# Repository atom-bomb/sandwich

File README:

Sandwich is a project to create low-cost electronics for 3D printing and CNC using an ATMEGA644p and TB6600 stepper drivers, not entirely unlike http://www.reprap.org/wiki/Gen7T and http://www.reprap.org/wiki/Sanguish.

The goal is to make an easily built, free and open design capable of running the Marlin firmware that can be built for around $40.

Design work is currently being done in the hobbyist-friendly Eagle CAD.
If the design exceeds the limits of the free version of Eagle CAD, the design will likely be ported to gEDA or another free CAD system in order to support the free and open design goal.

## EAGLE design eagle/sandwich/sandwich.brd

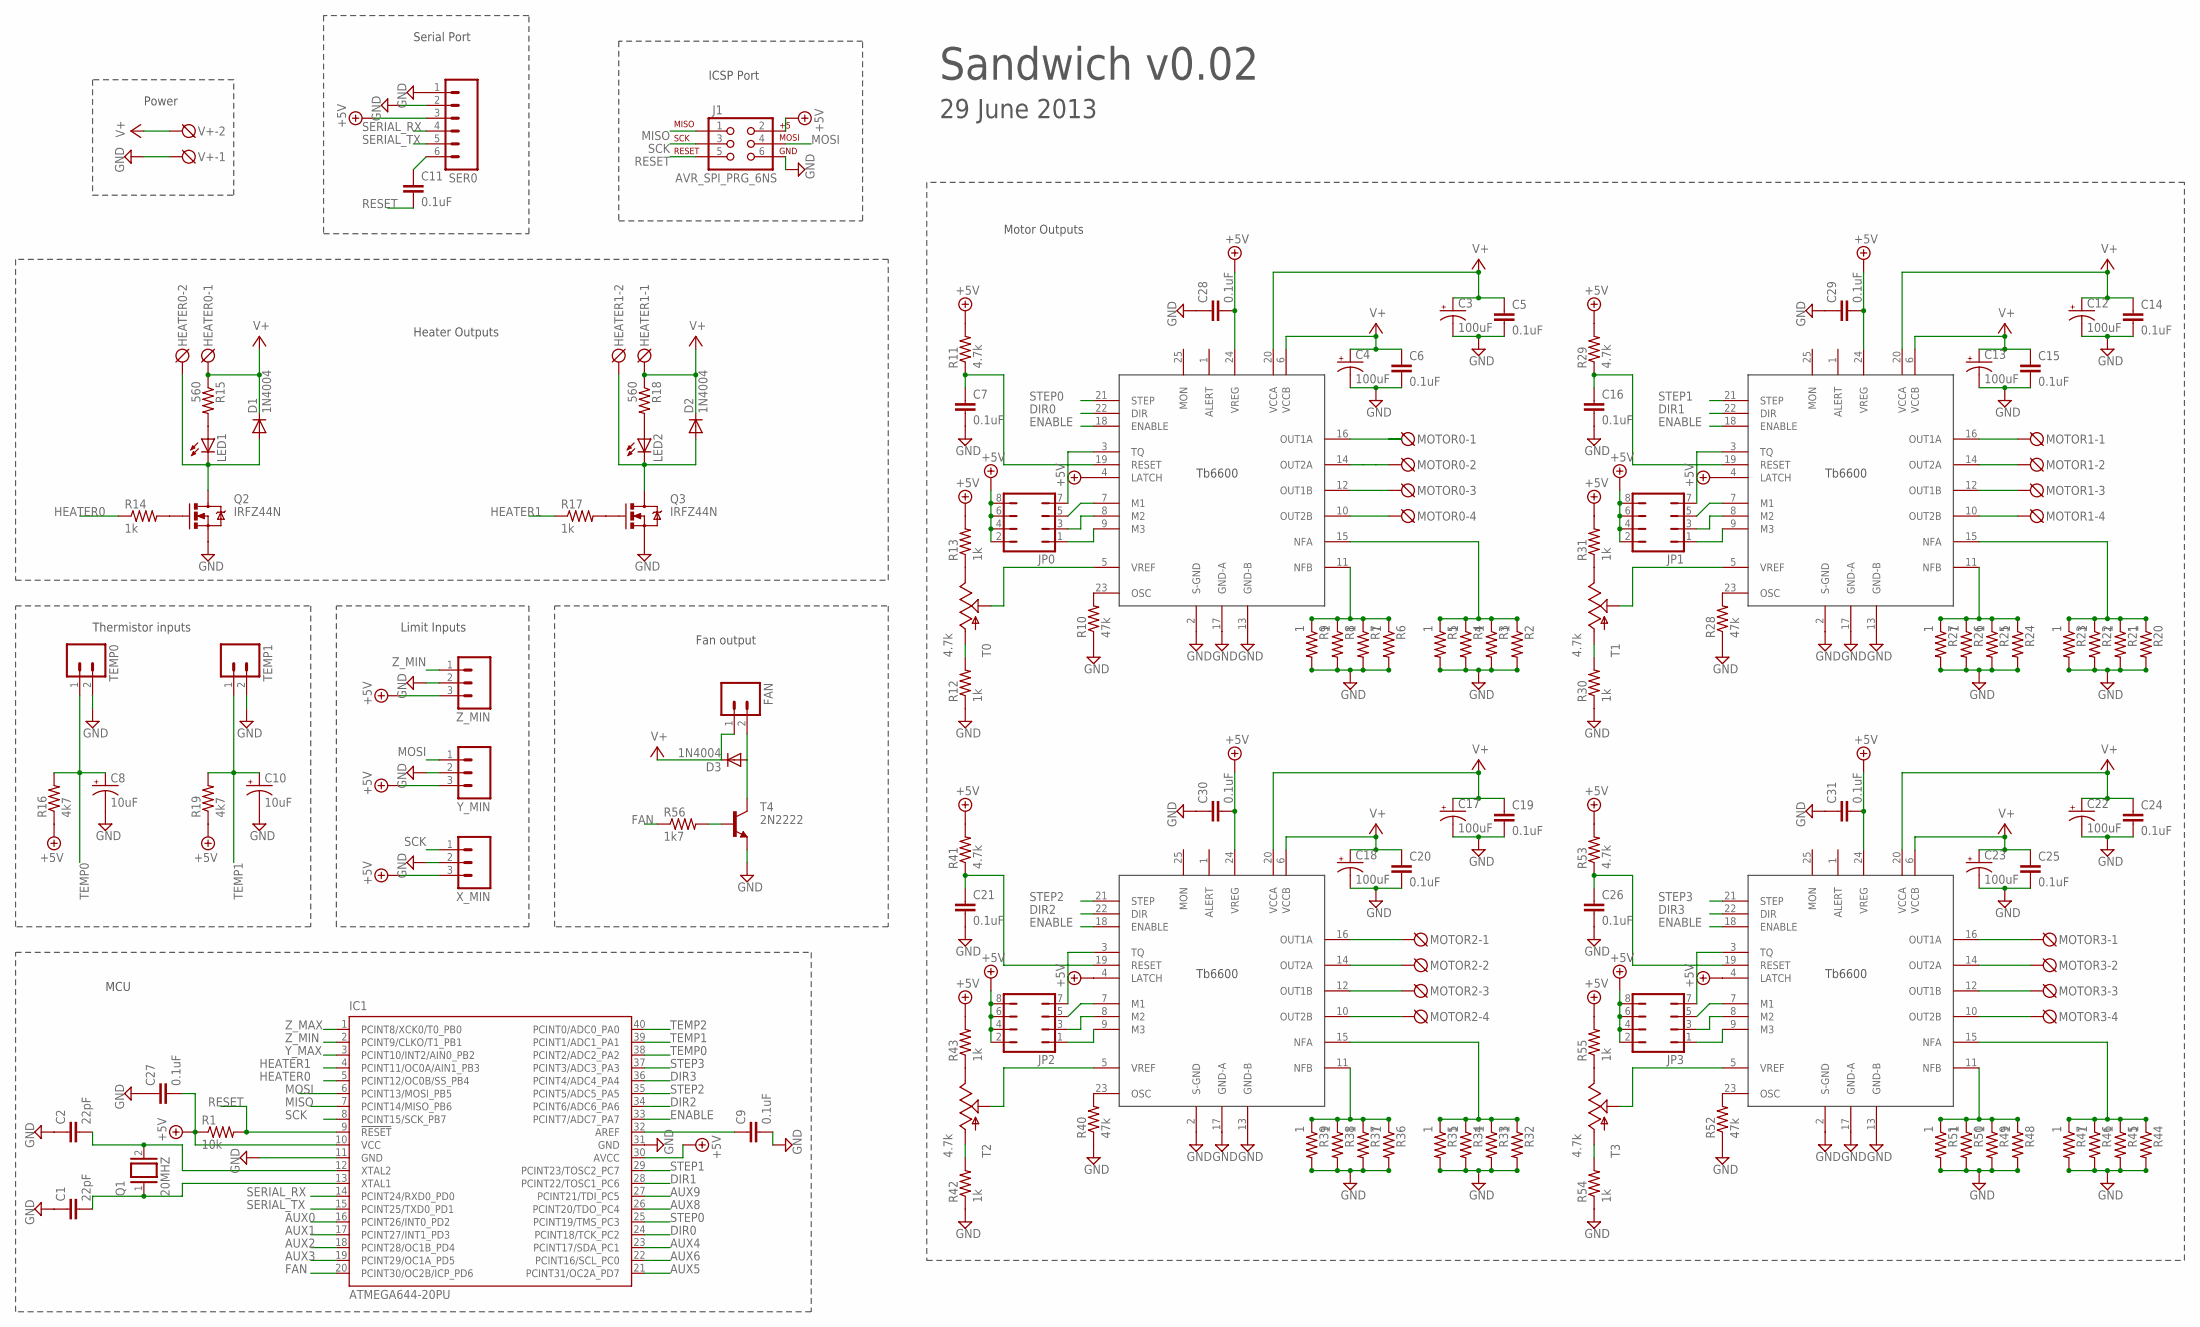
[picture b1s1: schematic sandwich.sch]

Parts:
C1, C2: 22pF; CAP-PTH-SMALL2
C3, C4, C12, C13, C17, C18, C22, C23: 100uF; CPOL-RADIAL-10UF-25V
C5, C6, C7, C9, C11, C14, C15, C16, C19, C20, C21, C24, C25, C26, C27, C28, C29, C30, C31: 0.1uF; CAP-PTH-SMALL
C8, C10: 10uF; CPOL-RADIAL-10UF-25V
D1, D2: 1N4004; DO41-10
D3: 1N4004; DIODE-1N4001
FAN: M02PTH3; 1X02_LONGPADS
HEATER0, HEATER1: DG3XX-02-3.5; DG350-3.5-02P
IC1: ATMEGA644-20PU; DIL40
J1: AVR_SPI_PRG_6NS; 2X3-NS
JP0, JP1, JP2, JP3: JP4Q
LED1, LED2: LED5MM
MOTOR0, MOTOR1, MOTOR2, MOTOR3: DG3XX-04-3.5; DG350-3.5-04P
Q1: 20MHZ; QS
Q2, Q3: IRFZ44N; TO220V
R1: 10k; 0204V
R2, R3, R4, R5, R6, R7, R8, R9, R20, R21, R22, R23, R24, R25, R26, R27, R32, R33, R34, R35, R36, R37, R38, R39, R44, R45, R46, R47, R48, R49, R50, R51: 1; 0204V
R10, R28, R40, R52: 47k; 0204V
R11, R29, R41, R53: 4.7k; 0204V
R12, R13, R14, R17, R30, R31, R42, R43, R54, R55: 1k; 0204V
R15, R18: 560; 0204V
R16, R19: 4k7; 0204V
R56: 1k7; 0204V
SER0: M06SIP; 1X06
T0, T1, T2, T3: 4.7k; TRIM_POT
T4: 2N2222; TO18
TEMP0, TEMP1: M02PTH3; 1X02_LONGPADS
U$1, U$2, U$3, U$4: TB6600HG; P-HZIP25-1.00G
V+: DG3XX-02-3.5; DG350-3.5-02P
X_MIN: M03LONGPADS; 1X03_LONGPADS
Y_MIN: M03LONGPADS; 1X03_LONGPADS
Z_MIN: M03LONGPADS; 1X03_LONGPADS

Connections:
+5V: C27.2, C28.2, C29.2, C30.2, C31.2, IC1.10 (VCC), IC1.30 (AVCC), J1.2, JP0.2, JP0.4, JP0.6, JP0.8, JP1.2, JP1.4, JP1.6, JP1.8, JP2.2, JP2.4, JP2.6, JP2.8, JP3.2, JP3.4, JP3.6, JP3.8, R1.1, R11.2, R13.2, R16.1, R19.1, R29.2, R31.2, R41.2, R43.2, R53.2, R55.2, SER0.3, U$1.4 (LATCH), U$1.24 (VREG), U$2.4 (LATCH), U$2.24 (VREG), U$3.4 (LATCH), U$3.24 (VREG), U$4.4 (LATCH), U$4.24 (VREG), X_MIN.3, Y_MIN.3, Z_MIN.3
AUX0: IC1.16 (PCINT26/INT0_PD2)
AUX1: IC1.17 (PCINT27/INT1_PD3)
AUX2: IC1.18 (PCINT28/OC1B_PD4)
AUX3: IC1.19 (PCINT29/OC1A_PD5)
AUX4: IC1.23 (PCINT17/SDA_PC1)
AUX5: IC1.21 (PCINT31/OC2A_PD7)
AUX6: IC1.22 (PCINT16/SCL_PC0)
AUX8: IC1.26 (PCINT20/TDO_PC4)
AUX9: IC1.27 (PCINT21/TDI_PC5)
DIR0: IC1.24 (PCINT18/TCK_PC2), U$1.22 (DIR)
DIR1: IC1.28 (PCINT22/TOSC1_PC6), U$2.22 (DIR)
DIR2: IC1.34 (PCINT6/ADC6_PA6), U$3.22 (DIR)
DIR3: IC1.36 (PCINT4/ADC4_PA4), U$4.22 (DIR)
ENABLE: IC1.33 (PCINT7/ADC7_PA7), U$1.18 (ENABLE), U$2.18 (ENABLE), U$3.18 (ENABLE), U$4.18 (ENABLE)
FAN: IC1.20 (PCINT30/OC2B/ICP_PD6), R56.1
GND: C1.1, C2.1, C3.2 (-), C4.2 (-), C5.2, C6.2, C7.2, C8.2 (-), C9.2, C10.2 (-), C12.2 (-), C13.2 (-), C14.2, C15.2, C16.2, C17.2 (-), C18.2 (-), C19.2, C20.2, C21.2, C22.2 (-), C23.2 (-), C24.2, C25.2, C26.2, C27.1, C28.1, C29.1, C30.1, C31.1, IC1.11 (GND), IC1.31 (GND), J1.6, Q2.3 (S), Q3.3 (S), R2.2, R3.2, R4.2, R5.2, R6.2, R7.2, R8.2, R9.2, R10.1, R12.1, R20.2, R21.2, R22.2, R23.2, R24.2, R25.2, R26.2, R27.2, R28.1, R30.1, R32.2, R33.2, R34.2, R35.2, R36.2, R37.2, R38.2, R39.2, R40.1, R42.1, R44.2, R45.2, R46.2, R47.2, R48.2, R49.2, R50.2, R51.2, R52.1, R54.1, SER0.1, SER0.2, T4.1 (E), TEMP0.2, TEMP1.2, U$1.2 (S-GND), U$1.13 (GND-B), U$1.17 (GND-A), U$2.2 (S-GND), U$2.13 (GND-B), U$2.17 (GND-A), U$3.2 (S-GND), U$3.13 (GND-B), U$3.17 (GND-A), U$4.2 (S-GND), U$4.13 (GND-B), U$4.17 (GND-A), V+.1, X_MIN.2, Y_MIN.2, Z_MIN.2
HEATER0: IC1.5 (PCINT12/OC0B/SS_PB4), R14.1
HEATER1: IC1.4 (PCINT11/OC0A/AIN1_PB3), R17.1
MISO: IC1.7 (PCINT14/MISO_PB6), J1.1
MOSI: IC1.6 (PCINT13/MOSI_PB5), J1.4, Y_MIN.1
unnamed: C2.2, IC1.12 (XTAL2), Q1.2
unnamed: C1.2, IC1.13 (XTAL1), Q1.1
unnamed: R10.2, U$1.23 (OSC)
unnamed: R2.1, R3.1, R4.1, R5.1, U$1.15 (NFA)
unnamed: R6.1, R7.1, R8.1, R9.1, U$1.11 (NFB)
unnamed: MOTOR0.4, U$1.10 (OUT2B)
unnamed: MOTOR0.3, U$1.12 (OUT1B)
unnamed: MOTOR0.2, U$1.14 (OUT2A)
unnamed: MOTOR0.1, U$1.16 (OUT1A)
unnamed: R12.2, T0.3 (A)
unnamed: R13.1, T0.2 (E)
unnamed: T0.1 (S), U$1.5 (VREF)
unnamed: Q2.1 (G), R14.2
unnamed: LED1.A, R15.2
unnamed: D1.A, HEATER0.2, LED1.K (C), Q2.2 (D)
unnamed: C7.1, R11.1, U$1.19 (RESET)
unnamed: C9.1, IC1.32 (AREF)
unnamed: JP0.1, U$1.9 (M3)
unnamed: Q3.1 (G), R17.2
unnamed: LED2.A, R18.2
unnamed: D2.A, HEATER1.2, LED2.K (C), Q3.2 (D)
unnamed: JP0.3, U$1.8 (M2)
unnamed: JP0.5, U$1.7 (M1)
unnamed: JP0.7, U$1.3 (TQ)
unnamed: C11.1, SER0.6
unnamed: D3.A, FAN.2, T4.3 (C)
unnamed: R20.1, R21.1, R22.1, R23.1, U$2.15 (NFA)
unnamed: R24.1, R25.1, R26.1, R27.1, U$2.11 (NFB)
unnamed: R28.2, U$2.23 (OSC)
unnamed: MOTOR1.1, U$2.16 (OUT1A)
unnamed: MOTOR1.2, U$2.14 (OUT2A)
unnamed: MOTOR1.3, U$2.12 (OUT1B)
unnamed: MOTOR1.4, U$2.10 (OUT2B)
unnamed: C16.1, R29.1, U$2.19 (RESET)
unnamed: R30.2, T1.3 (A)
unnamed: R31.1, T1.2 (E)
unnamed: T1.1 (S), U$2.5 (VREF)
unnamed: JP1.1, U$2.9 (M3)
unnamed: JP1.3, U$2.8 (M2)
unnamed: JP1.5, U$2.7 (M1)
unnamed: JP1.7, U$2.3 (TQ)
unnamed: R32.1, R33.1, R34.1, R35.1, U$3.15 (NFA)
unnamed: R36.1, R37.1, R38.1, R39.1, U$3.11 (NFB)
unnamed: R40.2, U$3.23 (OSC)
unnamed: MOTOR2.1, U$3.16 (OUT1A)
unnamed: MOTOR2.2, U$3.14 (OUT2A)
unnamed: MOTOR2.3, U$3.12 (OUT1B)
unnamed: MOTOR2.4, U$3.10 (OUT2B)
unnamed: C21.1, R41.1, U$3.19 (RESET)
unnamed: R42.2, T2.3 (A)
unnamed: R43.1, T2.2 (E)
unnamed: T2.1 (S), U$3.5 (VREF)
unnamed: JP2.1, U$3.9 (M3)
unnamed: JP2.3, U$3.8 (M2)
unnamed: JP2.5, U$3.7 (M1)
unnamed: JP2.7, U$3.3 (TQ)
unnamed: R44.1, R45.1, R46.1, R47.1, U$4.15 (NFA)
unnamed: R48.1, R49.1, R50.1, R51.1, U$4.11 (NFB)
unnamed: R52.2, U$4.23 (OSC)
unnamed: MOTOR3.1, U$4.16 (OUT1A)
unnamed: MOTOR3.2, U$4.14 (OUT2A)
unnamed: MOTOR3.3, U$4.12 (OUT1B)
unnamed: MOTOR3.4, U$4.10 (OUT2B)
unnamed: C26.1, R53.1, U$4.19 (RESET)
unnamed: R54.2, T3.3 (A)
unnamed: R55.1, T3.2 (E)
unnamed: T3.1 (S), U$4.5 (VREF)
unnamed: JP3.1, U$4.9 (M3)
unnamed: JP3.3, U$4.8 (M2)
unnamed: JP3.5, U$4.7 (M1)
unnamed: JP3.7, U$4.3 (TQ)
unnamed: R56.2, T4.2 (B)
RESET: C11.2, IC1.9 (!RESET), J1.5, R1.2
SCK: IC1.8 (PCINT15/SCK_PB7), J1.3, X_MIN.1
SERIAL_RX: IC1.14 (PCINT24/RXD0_PD0), SER0.4
SERIAL_TX: IC1.15 (PCINT25/TXD0_PD1), SER0.5
STEP0: IC1.25 (PCINT19/TMS_PC3), U$1.21 (STEP)
STEP1: IC1.29 (PCINT23/TOSC2_PC7), U$2.21 (STEP)
STEP2: IC1.35 (PCINT5/ADC5_PA5), U$3.21 (STEP)
STEP3: IC1.37 (PCINT3/ADC3_PA3), U$4.21 (STEP)
TEMP0: C8.1 (+), IC1.38 (PCINT2/ADC2_PA2), R16.2, TEMP0.1
TEMP1: C10.1 (+), IC1.39 (PCINT1/ADC1_PA1), R19.2, TEMP1.1
TEMP2: IC1.40 (PCINT0/ADC0_PA0)
V+: C3.1 (+), C4.1 (+), C5.1, C6.1, C12.1 (+), C13.1 (+), C14.1, C15.1, C17.1 (+), C18.1 (+), C19.1, C20.1, C22.1 (+), C23.1 (+), C24.1, C25.1, D1.C, D2.C, D3.C, FAN.1, HEATER0.1, HEATER1.1, R15.1, R18.1, U$1.6 (VCCB), U$1.20 (VCCA), U$2.6 (VCCB), U$2.20 (VCCA), U$3.6 (VCCB), U$3.20 (VCCA), U$4.6 (VCCB), U$4.20 (VCCA), V+.2
Y_MAX: IC1.3 (PCINT10/INT2/AIN0_PB2)
Z_MAX: IC1.1 (PCINT8/XCK0/T0_PB0)
Z_MIN: IC1.2 (PCINT9/CLKO/T1_PB1), Z_MIN.1

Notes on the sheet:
Thermistor inputs
Limit Inputs
Heater Outputs
Serial Port
ICSP Port
Power
Motor Outputs
MCU
Sandwich v0.02
29 June 2013
Fan output

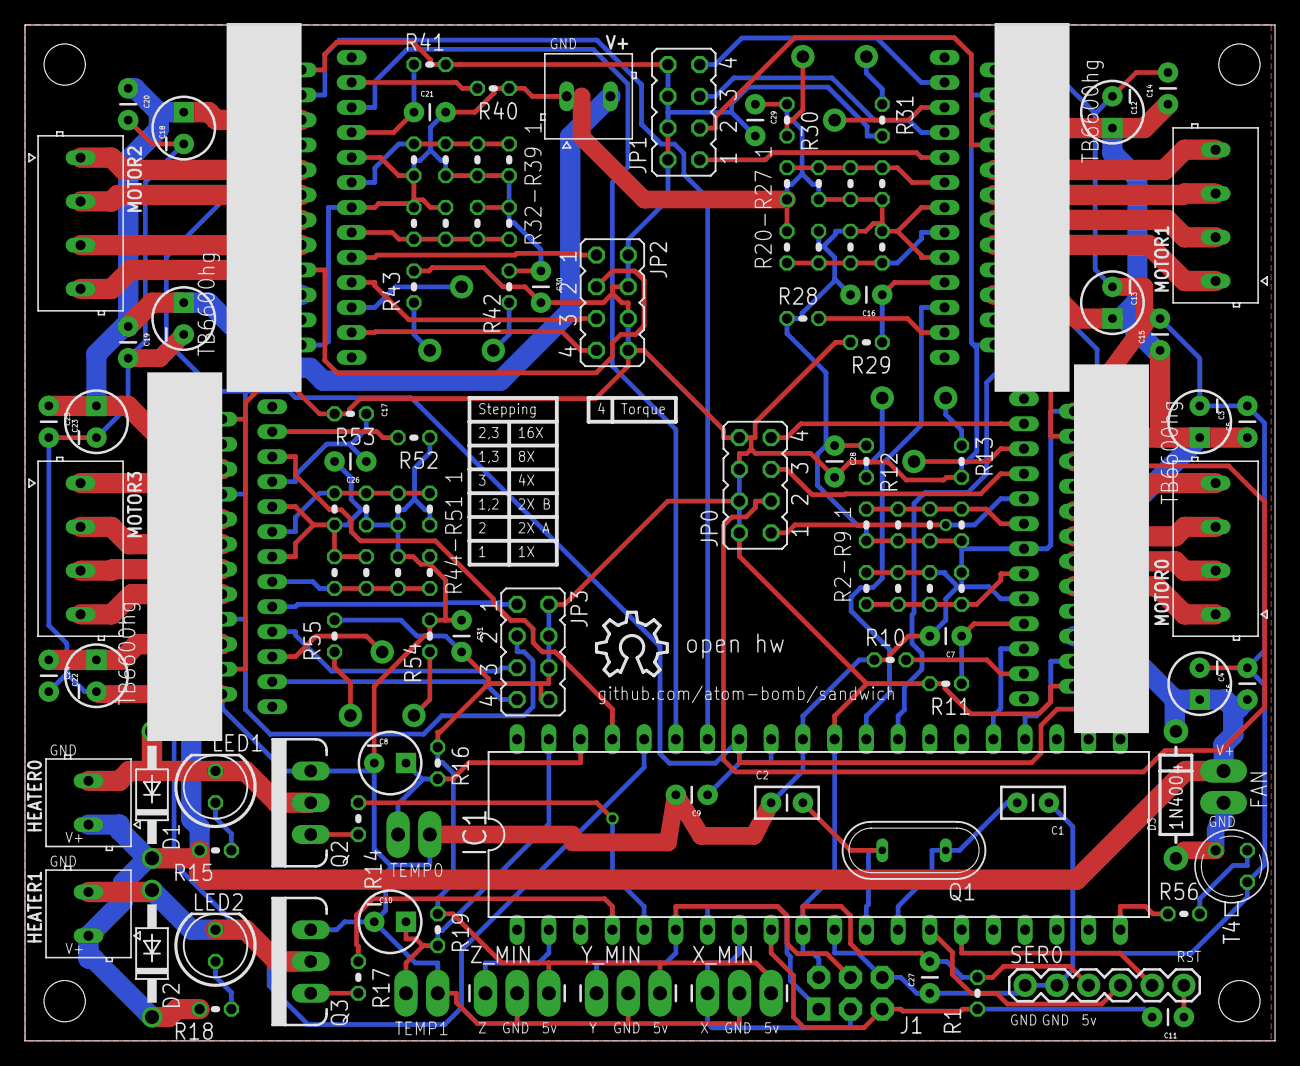
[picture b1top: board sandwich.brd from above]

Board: 2 copper layers, 100.0 x 81.3 mm, 129 parts (0 on the bottom side), 96 nets.

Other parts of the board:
U$5, U$6, U$7, U$8: STAND-OFF
U$9: OSHW_10X200_NOTEXT

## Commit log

2013-05-07 First commit of Sandwich, including a schematic!
2013-05-07 removed eagle backup files
2013-05-07 Added links to reprap.org
2013-05-07 gitignore eagle undo files
2013-05-07 issue#5: added decoupling caps
2013-05-07 fixed typo
2013-05-08 Changed all screw terminals to the smaller DG350
2013-05-08 reorganized for 11x17 printability, added title and date text
2013-05-09 AVR pin assignments are now the same as Gen7t. Motor enables are now combined.
2013-05-09 Changed all connectors except V+ and heaters to pin headers, removed axis max inputs
2013-05-11 The beginnings of a board layout
2013-05-15 Changed motor connectors back to screw terminals, added a fan output and routed the board layout.
2013-05-15 Changed trim pots to 4.7k
2013-06-01 This seems like a millable layout and routing
2013-06-25 added HZIP-25 package with measured TB6600HG dimensions.
2013-06-25 Updated TB6600 package, moved R56, changed 100uF caps to 16v, disabled GND and V+ thermals. Still needs TB6600HG layout adjustment and new routing
2013-06-28 A grid with some parts, suppliers and prices
2013-06-29 Moved FAN to a PWM output
2013-06-30 Adjusted layout for larger TB6600 package, routed with improved traces for V+ and GND
2013-07-01 Cleaned up the silkscreen layer
2013-07-03 beefed up some traces
2013-10-15 added AMT and Open HW logos
2013-12-04 Fatten up a few ground traces...just in case.
2013-12-05 eagle 6.5 + oshpark DRU compliance
2014-01-09 labeled GND, 5v and V+ on polarized connections
2014-01-12 Added documentation for jumper settings
2014-01-13 AMT logo is now oshpark-friendly

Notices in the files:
parts and their libraries:
SparkFun-Connectors: Licensing: CC v3.0 Share-Alike You are welcome to use this library for commercial purposes.
